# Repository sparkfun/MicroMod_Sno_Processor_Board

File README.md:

SparkFun MicroMod Alorium Sno M2 Processor Board
========================================

[*SparkFun MicroMod Alorium Sno M2 Processor Board (18030)*](https://www.sparkfun.com/products/18030)

The [MicroMod Alorium Sno M2 Processor Board](https://www.sparkfun.com/products/18030) features the Snō System on Module (SoM) from Alorium Technology adapted to the MicroMod M.2 processor form factor. Snō's FPGA provides a reconfigurable hardware platform that hosts an 8-bit AVR instruction set, compatible with the ATmega328, making Snō fully compatible with the Arduino IDE. Snō SoM has a compact footprint, making it ideal for space-constrained applications and an obvious addition to our MicroMod form factor for prototyping. 

Alorium Technology provides a library of custom logic called Xcelerator Blocks (XBs) through the Arduino IDE that accelerate specific functionality that is slow, problematic, or even impossible for an 8-bit microcontroller. This library includes XBs such as Servo Control, Quadrature, Floating Point Math, NeoPixel, and Enhanced Analog-to-Digital Converter. Alorium also notes a XB roadmap where future XBs will be implemented based on feedback
from early adopters and new potential customers. 

Repository Contents
-------------------

* **/Hardware** - Eagle design files (.brd, .sch)

Documentation
--------------
* **[Hookup Guide](https://learn.sparkfun.com/tutorials/micromod-alorium-sno-processor-board-hookup-guide)** - Basic hookup guide for the SparkFun MicroMod Alorium Sno Processor Board.

License Information
-------------------

This product is _**open source**_! 

Please review the LICENSE.md file for license information. 

If you have any questions or concerns on licensing, please contact technical support on our [SparkFun forums](https://forum.sparkfun.com/viewforum.php?f=152).

Distributed as-is; no warranty is given.

- Your friends at SparkFun.

_<COLLABORATION CREDIT>_

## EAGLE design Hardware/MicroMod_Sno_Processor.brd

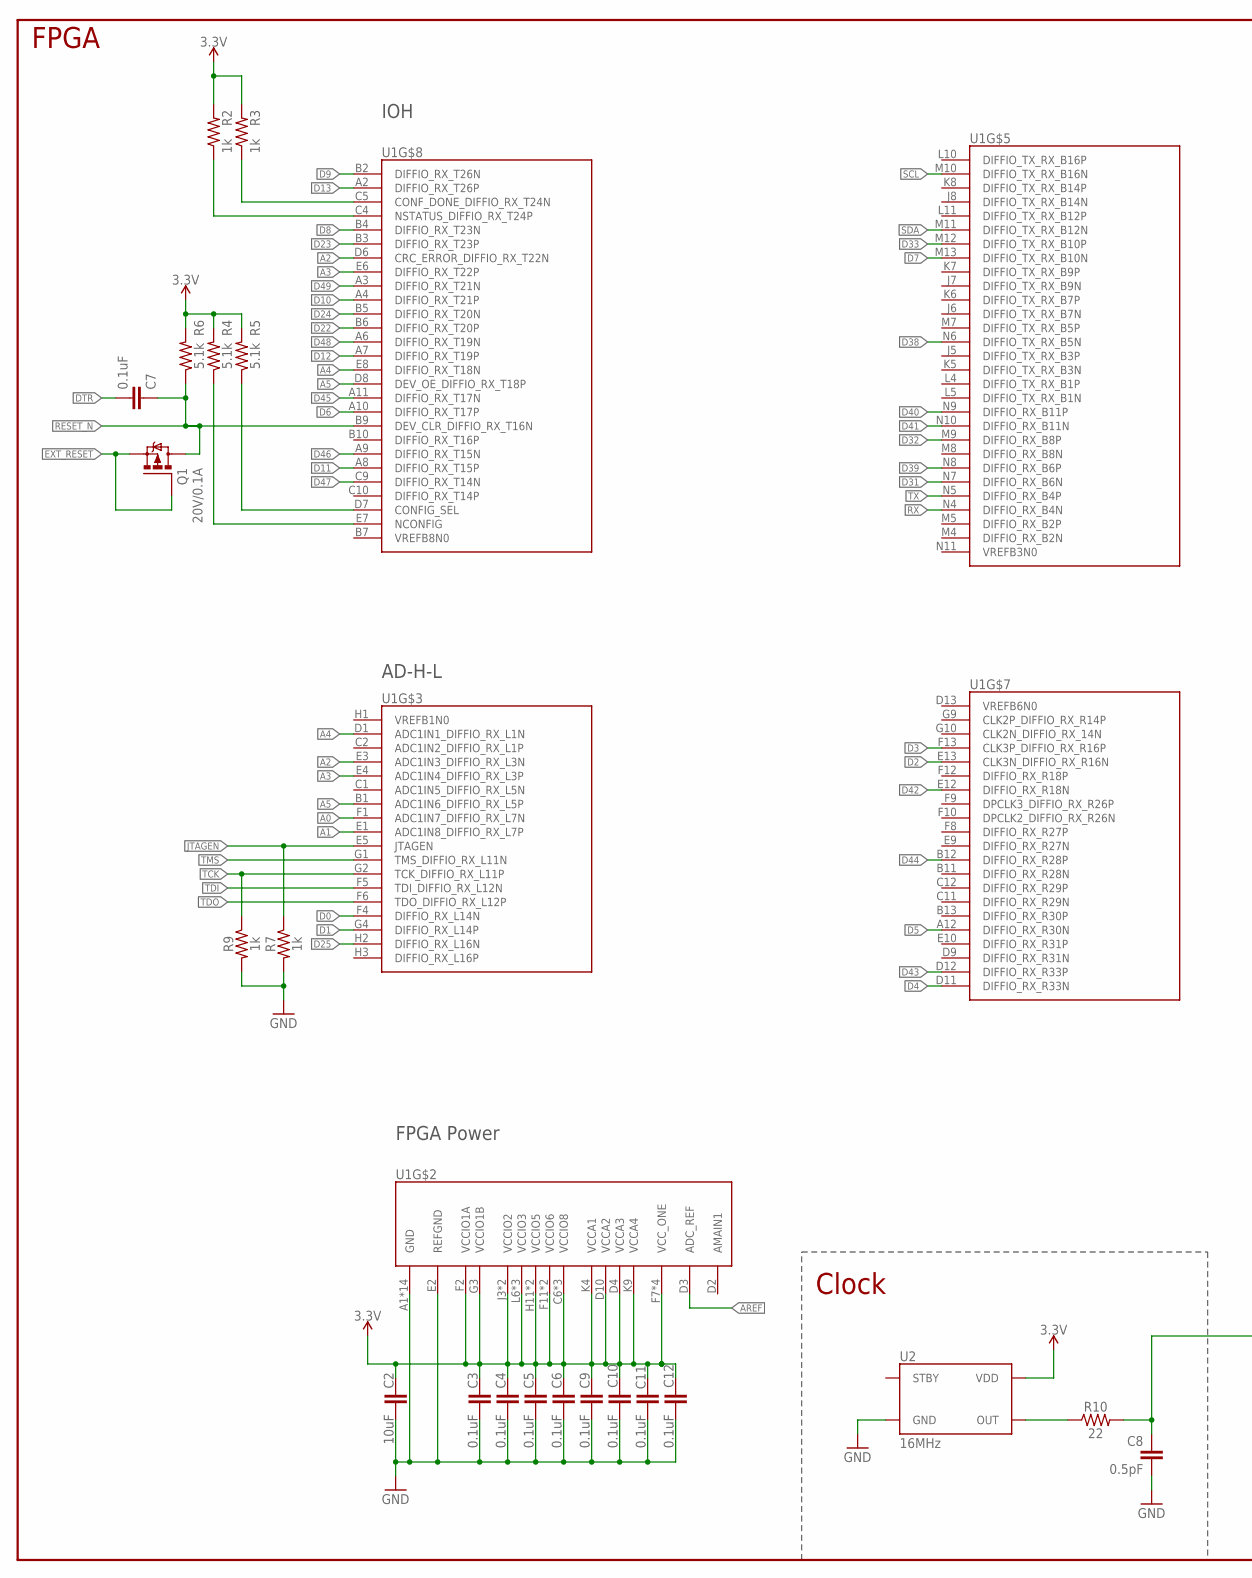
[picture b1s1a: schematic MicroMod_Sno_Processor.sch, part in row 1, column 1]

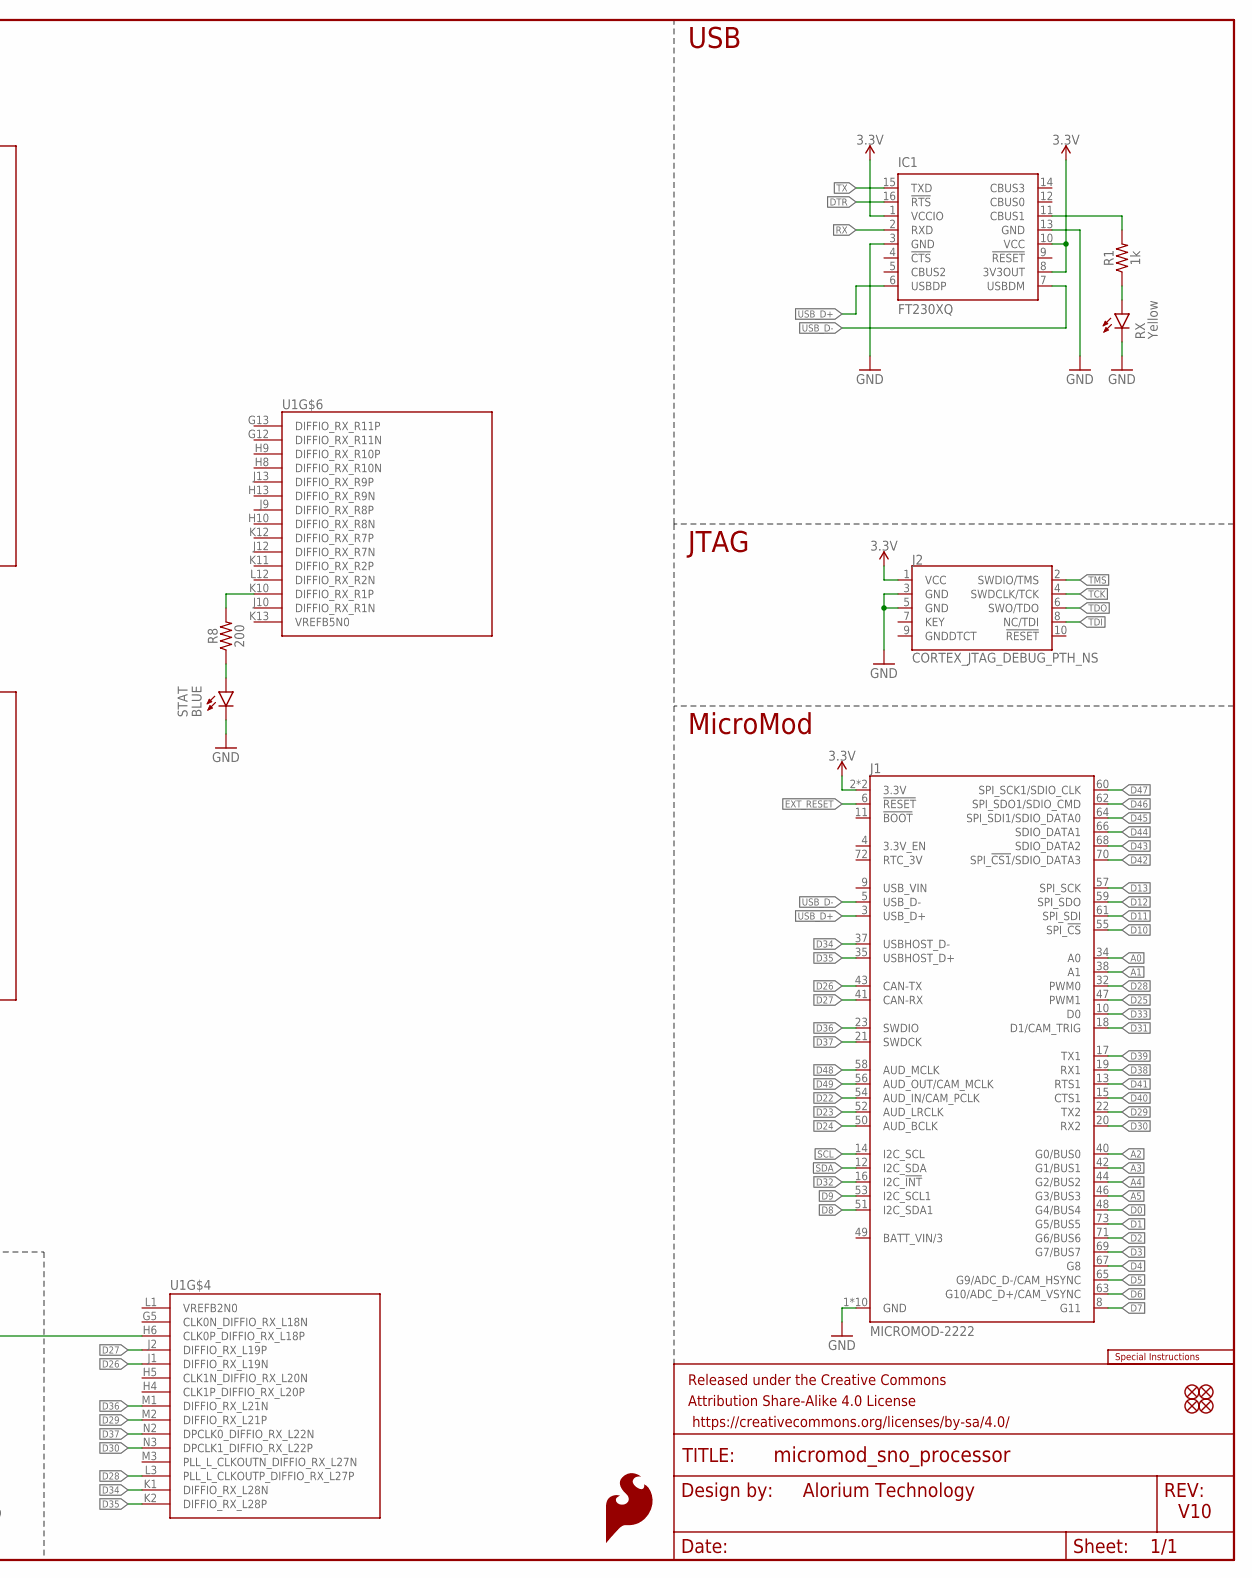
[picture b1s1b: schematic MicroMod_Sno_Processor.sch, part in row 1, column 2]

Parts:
C2: 10uF; 0402-TIGHT
C3, C4, C5, C6, C7, C9, C10, C11, C12: 0.1uF; 0402-TIGHT
C8: 0.5pF; 0402-TIGHT
FID1, FID2, FID3, FID4: FIDUCIAL1X2; FIDUCIAL-1X2
FRAME1: FRAME-LEDGER; CREATIVE_COMMONS
IC1: FT230XQ; QFN16
J1: MICROMOD-2222; M.2-CARD-E-22
J2: CORTEX_JTAG_DEBUG_PTH_NS; 2X5-PTH-1.27MM-NO_SILK
LOGO1: SPECIAL_INSTRUCTIONS-ORDERING; ORDERING_INSTRUCTIONS
LOGO2: SFE_LOGO_FLAME.1_INCH; SFE_LOGO_FLAME_.1
Q1: 20V/0.1A; SOT-416
R1, R2, R3, R7, R9: 1k; 0402-TIGHT
R4, R5, R6: 5.1k; 0402-TIGHT
R8: 200; 0402-TIGHT
R10: 22; 0402-TIGHT
RX: Yellow; LED-0603
STAT: BLUE; LED-0603
U1: 10M08SA; UBGA_169
U2: 16MHz; SMD20X16

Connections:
3.3V: C2.1, C3.1, C4.1, C5.1, C6.1, C9.1, C10.1, C11.1, C12.1, IC1.1 (VCCIO), IC1.8 (3V3OUT), IC1.10 (VCC), J1.2 (3.3V), J1.74 (3.3V), J2.1 (VCC), R2.2, R3.2, R4.2, R5.2, R6.2, U1.C6 (VCCIO8), U1.C7 (VCCIO8), U1.C8 (VCCIO8), U1.D4 (VCCA3), U1.D10 (VCCA2), U1.F2 (VCCIO1A), U1.F7 (VCC_ONE), U1.F11 (VCCIO6), U1.G3 (VCCIO1B), U1.G6 (VCC_ONE), U1.G8 (VCC_ONE), U1.G11 (VCCIO6), U1.H7 (VCC_ONE), U1.H11 (VCCIO5), U1.J3 (VCCIO2), U1.J11 (VCCIO5), U1.K3 (VCCIO2), U1.K4 (VCCA1), U1.K9 (VCCA4), U1.L6 (VCCIO3), U1.L7 (VCCIO3), U1.L8 (VCCIO3), U2.4 (VDD)
A0: J1.34 (A0), U1.F1 (ADC1IN7_DIFFIO_RX_L7N)
A1: J1.38 (A1), U1.E1 (ADC1IN8_DIFFIO_RX_L7P)
A2: J1.40 (G0/BUS0), U1.D6 (CRC_ERROR_DIFFIO_RX_T22N), U1.E3 (ADC1IN3_DIFFIO_RX_L3N)
A3: J1.42 (G1/BUS1), U1.E4 (ADC1IN4_DIFFIO_RX_L3P), U1.E6 (DIFFIO_RX_T22P)
A4: J1.44 (G2/BUS2), U1.D1 (ADC1IN1_DIFFIO_RX_L1N), U1.E8 (DIFFIO_RX_T18N)
A5: J1.46 (G3/BUS3), U1.B1 (ADC1IN6_DIFFIO_RX_L5P), U1.D8 (DEV_OE_DIFFIO_RX_T18P)
AREF: U1.D3 (ADC_REF)
CLK: C8.1, R10.2, U1.H6 (CLK0P_DIFFIO_RX_L18P)
D0: J1.48 (G4/BUS4), U1.F4 (DIFFIO_RX_L14N)
D1: J1.73 (G5/BUS5), U1.G4 (DIFFIO_RX_L14P)
D2: J1.71 (G6/BUS6), U1.E13 (CLK3N_DIFFIO_RX_R16N)
D3: J1.69 (G7/BUS7), U1.F13 (CLK3P_DIFFIO_RX_R16P)
D4: J1.67 (G8), U1.D11 (DIFFIO_RX_R33N)
D5: J1.65 (G9/ADC_D-/CAM_HSYNC), U1.A12 (DIFFIO_RX_R30N)
D6: J1.63 (G10/ADC_D+/CAM_VSYNC), U1.A10 (DIFFIO_RX_T17P)
D7: J1.8 (G11), U1.M13 (DIFFIO_TX_RX_B10N)
D8: J1.51 (I2C_SDA1), U1.B4 (DIFFIO_RX_T23N)
D9: J1.53 (I2C_SCL1), U1.B2 (DIFFIO_RX_T26N)
D10: J1.55 (SPI_!CS!), U1.A4 (DIFFIO_RX_T21P)
D11: J1.61 (SPI_SDI), U1.A8 (DIFFIO_RX_T15P)
D12: J1.59 (SPI_SDO), U1.A7 (DIFFIO_RX_T19P)
D13: J1.57 (SPI_SCK), U1.A2 (DIFFIO_RX_T26P)
D22: J1.54 (AUD_IN/CAM_PCLK), U1.B6 (DIFFIO_RX_T20P)
D23: J1.52 (AUD_LRCLK), U1.B3 (DIFFIO_RX_T23P)
D24: J1.50 (AUD_BCLK), U1.B5 (DIFFIO_RX_T20N)
D25: J1.47 (PWM1), U1.H2 (DIFFIO_RX_L16N)
D26: J1.43 (CAN-TX), U1.J1 (DIFFIO_RX_L19N)
D27: J1.41 (CAN-RX), U1.J2 (DIFFIO_RX_L19P)
D28: J1.32 (PWM0), U1.L3 (PLL_L_CLKOUTP_DIFFIO_RX_L27P)
D29: J1.22 (TX2), U1.M2 (DIFFIO_RX_L21P)
D30: J1.20 (RX2), U1.N3 (DPCLK1_DIFFIO_RX_L22P)
D31: J1.18 (D1/CAM_TRIG), U1.N7 (DIFFIO_RX_B6N)
D32: J1.16 (I2C_!INT!), U1.M9 (DIFFIO_RX_B8P)
D33: J1.10 (D0), U1.M12 (DIFFIO_TX_RX_B10P)
D34: J1.37 (USBHOST_D-), U1.K1 (DIFFIO_RX_L28N)
D35: J1.35 (USBHOST_D+), U1.K2 (DIFFIO_RX_L28P)
D36: J1.23 (SWDIO), U1.M1 (DIFFIO_RX_L21N)
D37: J1.21 (SWDCK), U1.N2 (DPCLK0_DIFFIO_RX_L22N)
D38: J1.19 (RX1), U1.N6 (DIFFIO_TX_RX_B5N)
D39: J1.17 (TX1), U1.N8 (DIFFIO_RX_B6P)
D40: J1.15 (CTS1), U1.N9 (DIFFIO_RX_B11P)
D41: J1.13 (RTS1), U1.N10 (DIFFIO_RX_B11N)
D42: J1.70 (SPI_!CS1!/SDIO_DATA3), U1.E12 (DIFFIO_RX_R18N)
D43: J1.68 (SDIO_DATA2), U1.D12 (DIFFIO_RX_R33P)
D44: J1.66 (SDIO_DATA1), U1.B12 (DIFFIO_RX_R28P)
D45: J1.64 (SPI_SDI1/SDIO_DATA0), U1.A11 (DIFFIO_RX_T17N)
D46: J1.62 (SPI_SDO1/SDIO_CMD), U1.A9 (DIFFIO_RX_T15N)
D47: J1.60 (SPI_SCK1/SDIO_CLK), U1.C9 (DIFFIO_RX_T14N)
D48: J1.58 (AUD_MCLK), U1.A6 (DIFFIO_RX_T19N)
D49: J1.56 (AUD_OUT/CAM_MCLK), U1.A3 (DIFFIO_RX_T21N)
DTR: C7.2, IC1.16 (!RTS)
EXT_RESET: J1.6 (!RESET!), Q1.P1 (G), Q1.P2 (S)
GND: C2.2, C3.2, C4.2, C5.2, C6.2, C8.2, C9.2, C10.2, C11.2, C12.2, IC1.3 (GND), IC1.13 (GND), J1.1 (GND), J1.7 (GND), J1.33 (GND), J1.36 (GND), J1.39 (GND), J1.45 (GND), J1.75 (GND), J1.GND1 (GND), J1.GND2 (GND), J1.GND3 (GND), J2.3 (GND), J2.5 (GND), R7.2, R9.2, RX.C, STAT.C, U1.A1 (GND), U1.A13 (GND), U1.B8 (GND), U1.C3 (GND), U1.D5 (GND), U1.E2 (REFGND), U1.E11 (GND), U1.F3 (GND), U1.G7 (GND), U1.H12 (GND), U1.J4 (GND), U1.L9 (GND), U1.M6 (GND), U1.N1 (GND), U1.N13 (GND), U2.2 (GND)
JTAGEN: R7.1, U1.E5 (JTAGEN)
unnamed: R1.1, RX.A
unnamed: R3.1, U1.C5 (CONF_DONE_DIFFIO_RX_T24N)
unnamed: R8.1, STAT.A
unnamed: R2.1, U1.C4 (NSTATUS_DIFFIO_RX_T24P)
unnamed: R5.1, U1.D7 (CONFIG_SEL)
NCONFIG: R4.1, U1.E7 (NCONFIG)
OSC: R10.1, U2.3 (OUT)
RESET_N: C7.1, Q1.P3 (D), R6.1, U1.B9 (DEV_CLR_DIFFIO_RX_T16N)
RX: IC1.2 (RXD), U1.N4 (DIFFIO_RX_B4N)
RXLED: IC1.11 (CBUS1), R1.2
SCL: J1.14 (I2C_SCL), U1.M10 (DIFFIO_TX_RX_B16N)
SDA: J1.12 (I2C_SDA), U1.M11 (DIFFIO_TX_RX_B12N)
STAT: R8.2, U1.K10 (DIFFIO_RX_R1P)
TCK: J2.4 (SWDCLK/TCK), R9.1, U1.G2 (TCK_DIFFIO_RX_L11P)
TDI: J2.8 (NC/TDI), U1.F5 (TDI_DIFFIO_RX_L12N)
TDO: J2.6 (SWO/TDO), U1.F6 (TDO_DIFFIO_RX_L12P)
TMS: J2.2 (SWDIO/TMS), U1.G1 (TMS_DIFFIO_RX_L11N)
TX: IC1.15 (TXD), U1.N5 (DIFFIO_RX_B4P)
USB_D+: IC1.6 (USBDP), J1.3 (USB_D+)
USB_D-: IC1.7 (USBDM), J1.5 (USB_D-)

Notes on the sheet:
IOH
AD-H-L
FPGA Power
Clock
USB
FPGA
JTAG
MicroMod
V10
Alorium Technology

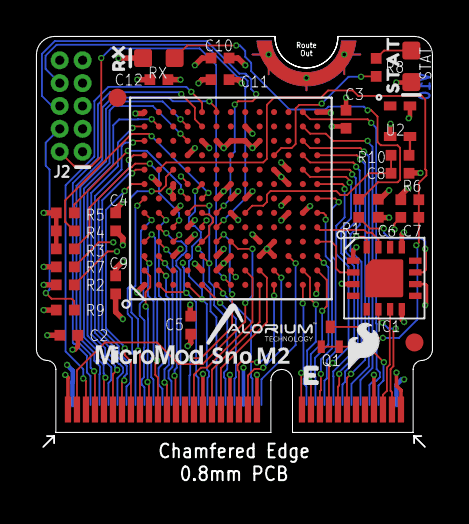
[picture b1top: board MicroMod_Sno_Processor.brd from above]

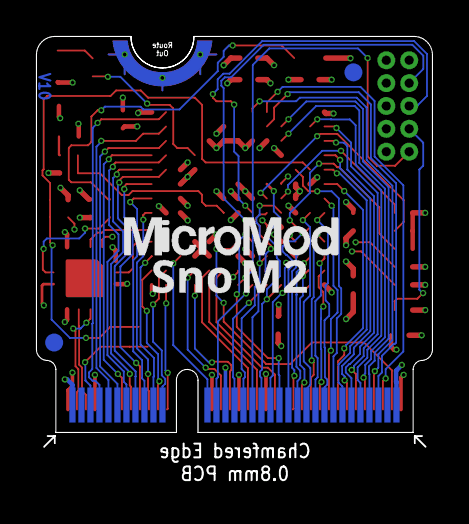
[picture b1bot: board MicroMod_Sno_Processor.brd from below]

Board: 4 copper layers, 21.9 x 25.0 mm, 38 parts (2 on the bottom side), 74 nets.

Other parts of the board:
U$1: STAT0
U$2: RX0

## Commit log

2021-05-04 V10 Update
    Updated routing for DFM and proto issues
2021-05-06 V10 QC changes
    - Added voltage range to FPGA
    - Updated RX LED to yellow
    - Updated PROD_ID for 22 ohm resistor
2021-05-07 Updated oscillator
    Updated oscillator to a smaller 2.0x1.6mm package
2021-05-07 Update MicroMod_Sno_Processor.sch
    Added VCC range note back to schematic
2021-05-07 Added panel gerbers

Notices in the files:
parts and their libraries:
SparkFun-Resistors: Licensing: Creative Commons ShareAlike 4.0 International - https://creativecommons.org/licenses/by-sa/4.0
SparkFun-Aesthetics: Released under the Creative Commons Attribution Share-Alike 4.0 License
SparkFun-Aesthetics: https://creativecommons.org/licenses/by-sa/4.0
